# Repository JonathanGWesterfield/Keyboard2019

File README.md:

# Keyboard2019
Holds files for PCB and CAD layout for a left handed cherry mx keyboard

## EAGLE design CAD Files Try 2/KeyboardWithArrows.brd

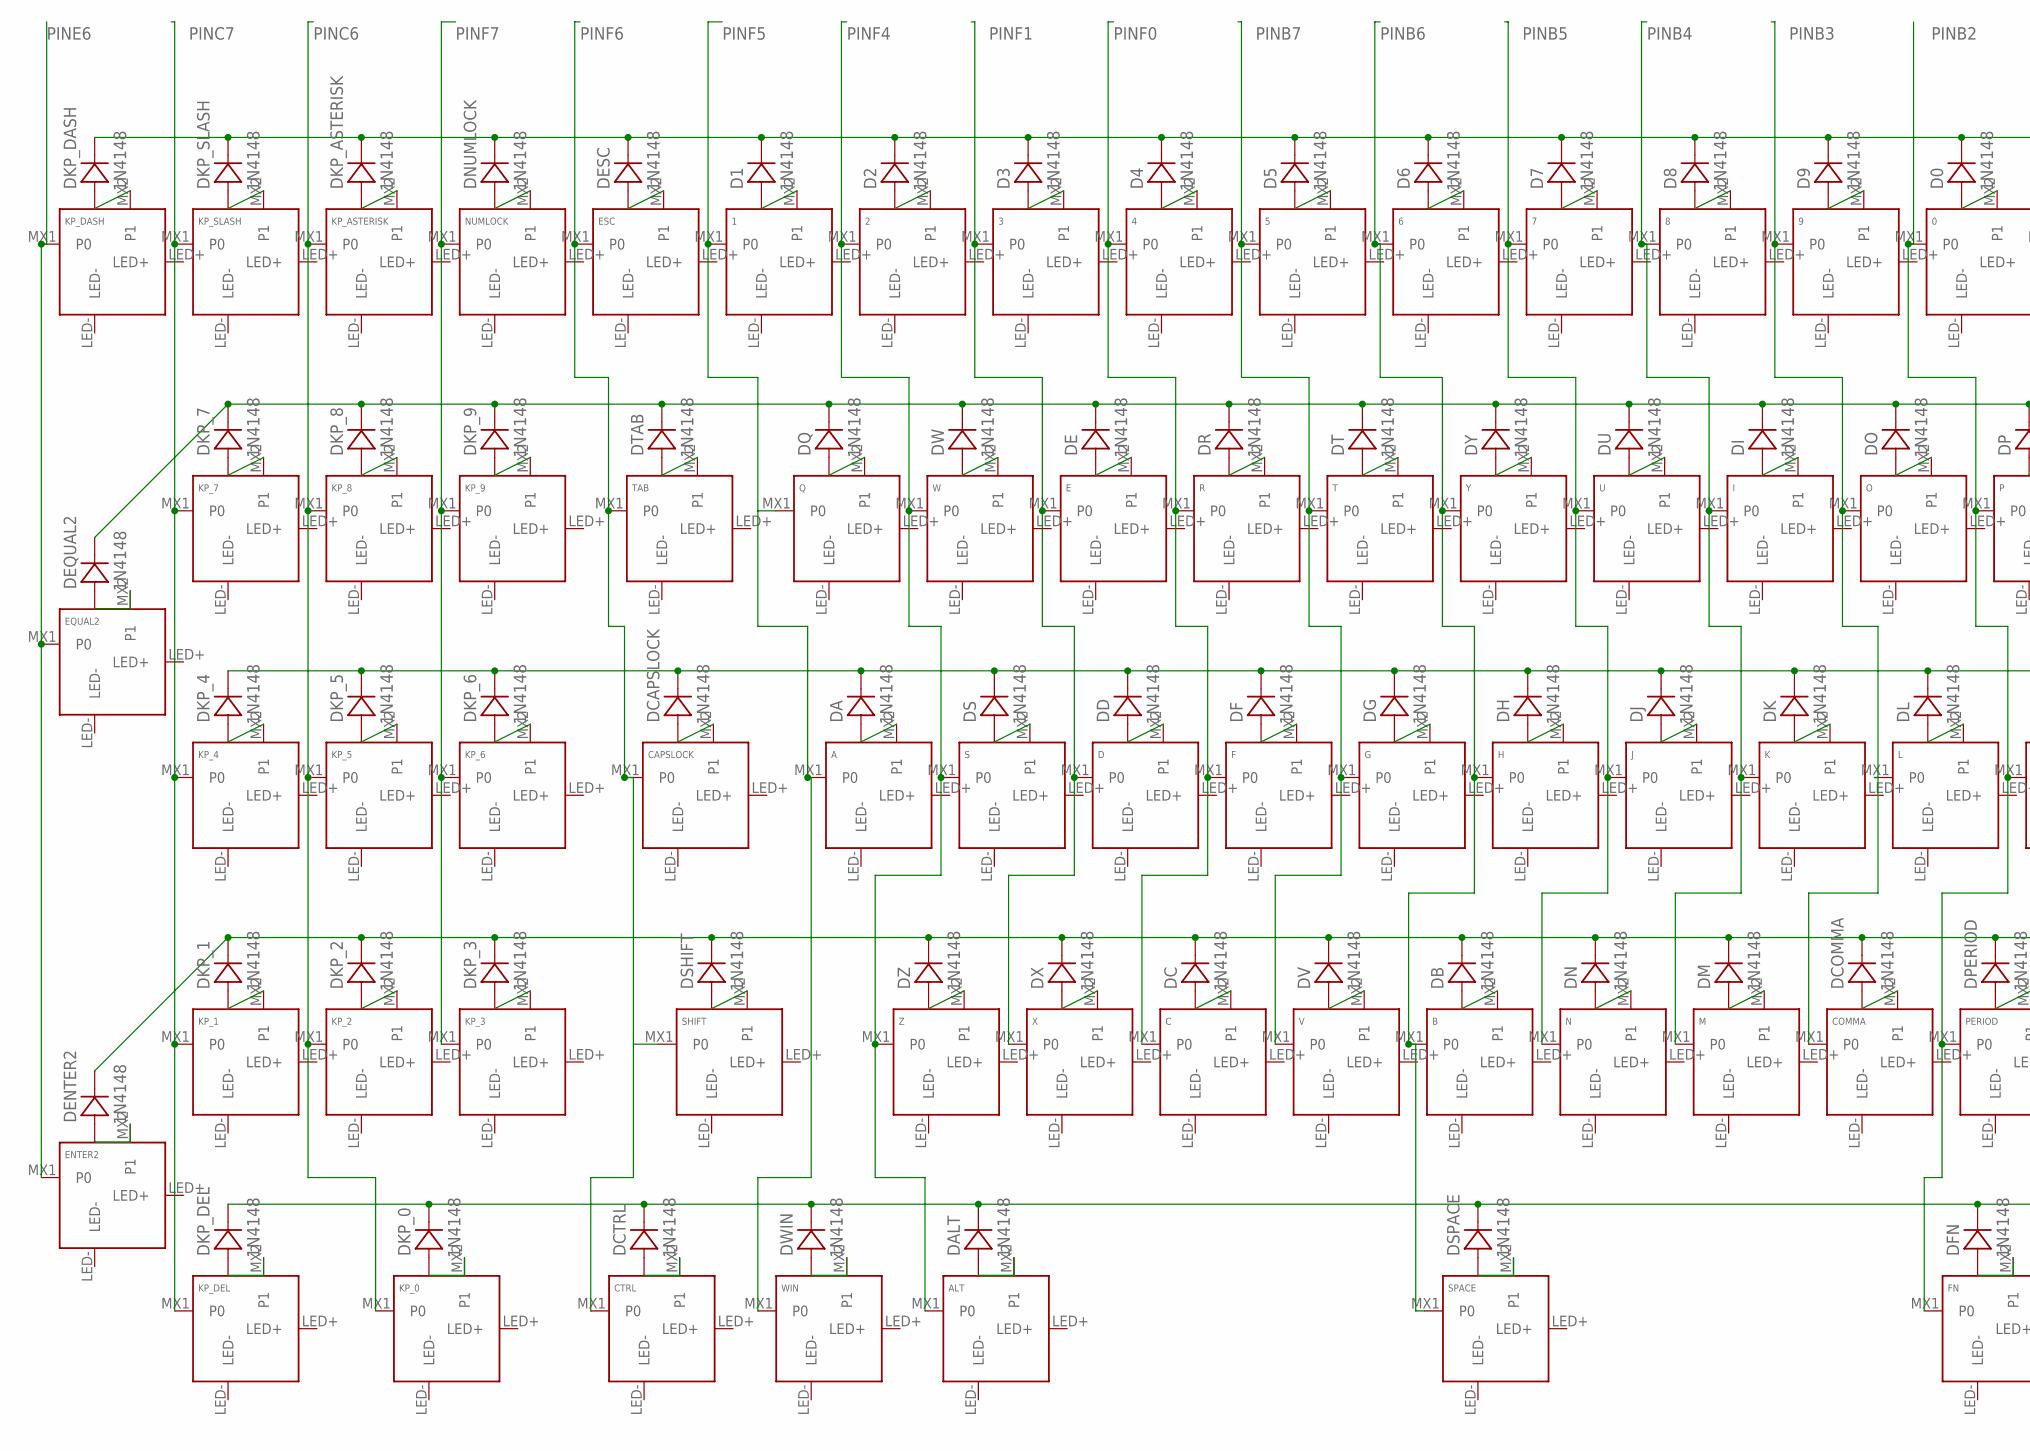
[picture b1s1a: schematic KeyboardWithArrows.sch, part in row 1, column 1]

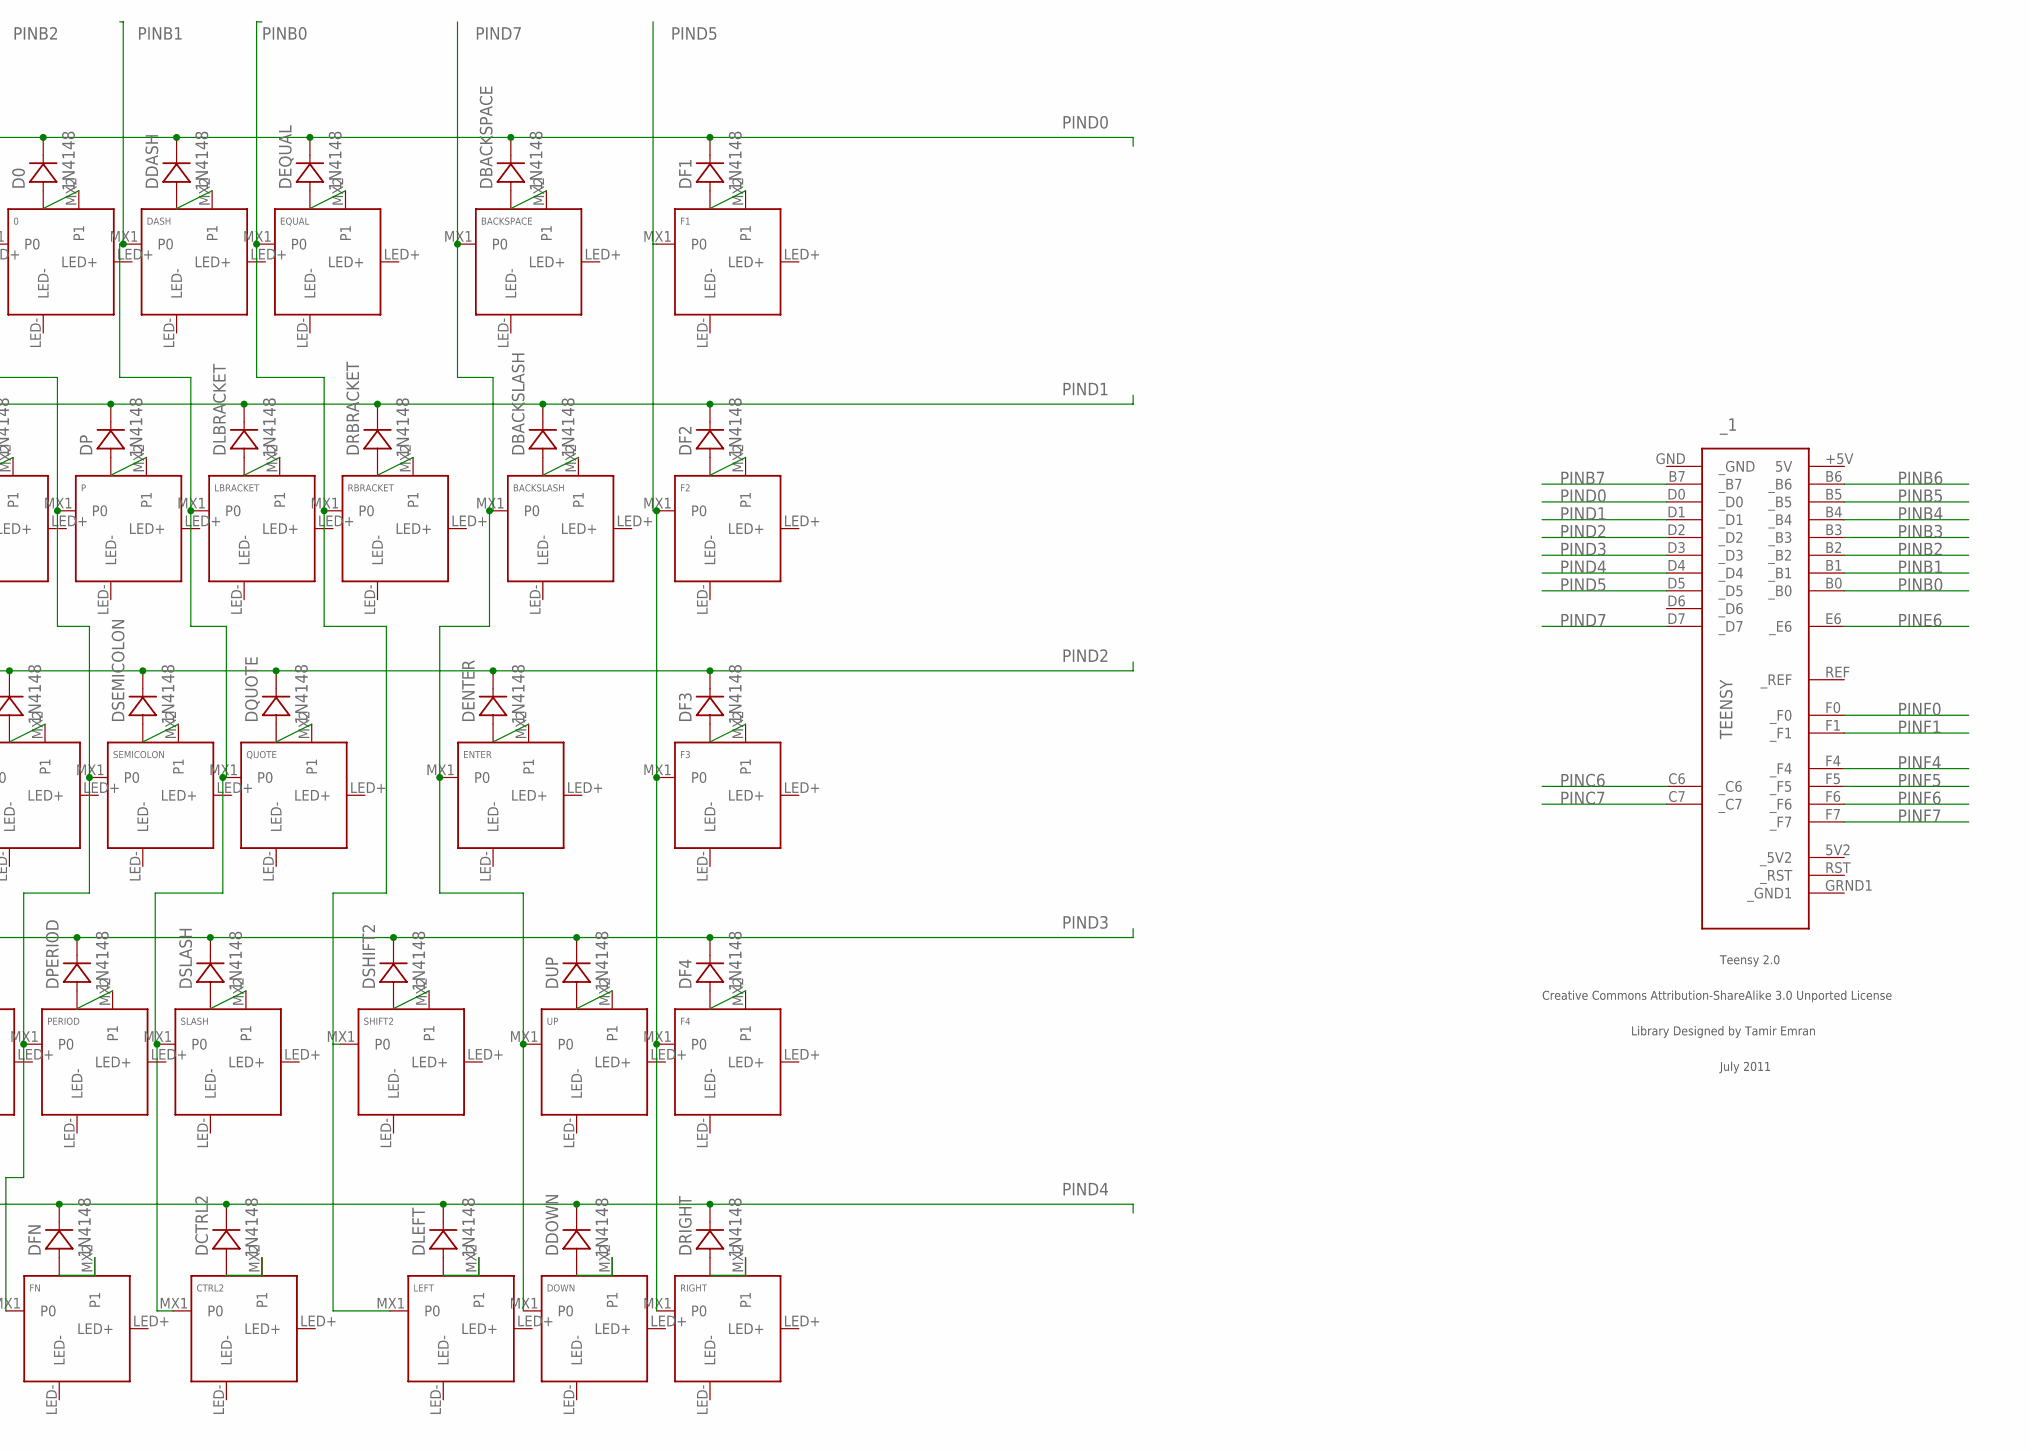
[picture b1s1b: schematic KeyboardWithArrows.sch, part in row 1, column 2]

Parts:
0, 1, 2, 3, 4, 5, 6, 7, 8, 9: KEYSWITCH-LED-MX-1U-LED; MX-1U-LED
A: KEYSWITCH-LED-MX-1U-LED; MX-1U-LED
ALT: KEYSWITCH-LED-MX-1U-LED; MX-1U-LED
B: KEYSWITCH-LED-MX-1U-LED; MX-1U-LED
BACKSLASH: KEYSWITCH-LED-MX-1U-LED; MX-1U-LED
BACKSPACE: KEYSWITCH-LED-MX-2U-LED; MX-2U-LED
C: KEYSWITCH-LED-MX-1U-LED; MX-1U-LED
CAPSLOCK: KEYSWITCH-LED-MX-1U-LED; MX-1U-LED
COMMA: KEYSWITCH-LED-MX-1U-LED; MX-1U-LED
CTRL, CTRL2: KEYSWITCH-LED-MX-1U-LED; MX-1U-LED
D: KEYSWITCH-LED-MX-1U-LED; MX-1U-LED
D0, D1, D2, D3, D4, D5, D6, D7, D8, D9: 1N4148; DO-35
DA: 1N4148; DO-35
DALT: 1N4148; DO-35
DASH: KEYSWITCH-LED-MX-1U-LED; MX-1U-LED
DB: 1N4148; DO-35
DBACKSLASH: 1N4148; DO-35
DBACKSPACE: 1N4148; DO-35
DC: 1N4148; DO-35
DCAPSLOCK: 1N4148; DO-35
DCOMMA: 1N4148; DO-35
DCTRL, DCTRL2: 1N4148; DO-35
DD: 1N4148; DO-35
DDASH: 1N4148; DO-35
DDOWN: 1N4148; DO-35
DE: 1N4148; DO-35
DENTER, DENTER2: 1N4148; DO-35
DEQUAL, DEQUAL2: 1N4148; DO-35
DESC: 1N4148; DO-35
DF, DF1, DF2, DF3, DF4: 1N4148; DO-35
DFN: 1N4148; DO-35
DG: 1N4148; DO-35
DH: 1N4148; DO-35
DI: 1N4148; DO-35
DJ: 1N4148; DO-35
DK: 1N4148; DO-35
DKP_0, DKP_1, DKP_2, DKP_3, DKP_4, DKP_5, DKP_6, DKP_7, DKP_8, DKP_9: 1N4148; DO-35
DKP_ASTERISK: 1N4148; DO-35
DKP_DASH: 1N4148; DO-35
DKP_DEL: 1N4148; DO-35
DKP_SLASH: 1N4148; DO-35
DL: 1N4148; DO-35
DLBRACKET: 1N4148; DO-35
DLEFT: 1N4148; DO-35
DM: 1N4148; DO-35
DN: 1N4148; DO-35
DNUMLOCK: 1N4148; DO-35
DO: 1N4148; DO-35
DOWN: KEYSWITCH-LED-MX-1U-LED; MX-1U-LED
DP: 1N4148; DO-35
DPERIOD: 1N4148; DO-35
DQ: 1N4148; DO-35
DQUOTE: 1N4148; DO-35
DR: 1N4148; DO-35
DRBRACKET: 1N4148; DO-35
DRIGHT: 1N4148; DO-35
DS: 1N4148; DO-35
DSEMICOLON: 1N4148; DO-35
DSHIFT, DSHIFT2: 1N4148; DO-35
DSLASH: 1N4148; DO-35
DSPACE: 1N4148; DO-35
DT: 1N4148; DO-35
DTAB: 1N4148; DO-35
DU: 1N4148; DO-35
DUP: 1N4148; DO-35
DV: 1N4148; DO-35
DW: 1N4148; DO-35
DWIN: 1N4148; DO-35
DX: 1N4148; DO-35
DY: 1N4148; DO-35
DZ: 1N4148; DO-35
E: KEYSWITCH-LED-MX-1U-LED; MX-1U-LED
ENTER: KEYSWITCH-LED-MX-2U-LED; MX-2U-LED
ENTER2: KEYSWITCH-LED-MX-1U-LED; MX-1U-LED
EQUAL, EQUAL2: KEYSWITCH-LED-MX-1U-LED; MX-1U-LED
ESC: KEYSWITCH-LED-MX-1U-LED; MX-1U-LED
F, F1, F2, F3, F4: KEYSWITCH-LED-MX-1U-LED; MX-1U-LED
FN: KEYSWITCH-LED-MX-1U-LED; MX-1U-LED
G: KEYSWITCH-LED-MX-1U-LED; MX-1U-LED
H: KEYSWITCH-LED-MX-1U-LED; MX-1U-LED
I: KEYSWITCH-LED-MX-1U-LED; MX-1U-LED
J: KEYSWITCH-LED-MX-1U-LED; MX-1U-LED
K: KEYSWITCH-LED-MX-1U-LED; MX-1U-LED
KP_0: KEYSWITCH-LED-MX-2U-LED; MX-2U-LED
KP_1, KP_2, KP_3, KP_4, KP_5, KP_6, KP_7, KP_8, KP_9: KEYSWITCH-LED-MX-1U-LED; MX-1U-LED
KP_ASTERISK: KEYSWITCH-LED-MX-1U-LED; MX-1U-LED
KP_DASH: KEYSWITCH-LED-MX-1U-LED; MX-1U-LED
KP_DEL: KEYSWITCH-LED-MX-1U-LED; MX-1U-LED
KP_SLASH: KEYSWITCH-LED-MX-1U-LED; MX-1U-LED
L: KEYSWITCH-LED-MX-1U-LED; MX-1U-LED
LBRACKET: KEYSWITCH-LED-MX-1U-LED; MX-1U-LED
LEFT: KEYSWITCH-LED-MX-1U-LED; MX-1U-LED
M: KEYSWITCH-LED-MX-1U-LED; MX-1U-LED
N: KEYSWITCH-LED-MX-1U-LED; MX-1U-LED
NUMLOCK: KEYSWITCH-LED-MX-1U-LED; MX-1U-LED
O: KEYSWITCH-LED-MX-1U-LED; MX-1U-LED
P: KEYSWITCH-LED-MX-1U-LED; MX-1U-LED
PERIOD: KEYSWITCH-LED-MX-1U-LED; MX-1U-LED
Q: KEYSWITCH-LED-MX-1U-LED; MX-1U-LED
QUOTE: KEYSWITCH-LED-MX-1U-LED; MX-1U-LED
R: KEYSWITCH-LED-MX-1U-LED; MX-1U-LED
RBRACKET: KEYSWITCH-LED-MX-1U-LED; MX-1U-LED
RIGHT: KEYSWITCH-LED-MX-1U-LED; MX-1U-LED
S: KEYSWITCH-LED-MX-1U-LED; MX-1U-LED
SEMICOLON: KEYSWITCH-LED-MX-1U-LED; MX-1U-LED
SHIFT: KEYSWITCH-LED-MX-2U-LED; MX-2U-LED
SHIFT2: KEYSWITCH-LED-MX-1U-LED; MX-1U-LED
SLASH: KEYSWITCH-LED-MX-1U-LED; MX-1U-LED
SPACE: KEYSWITCH-LED-MX-6.25U-LED; MX-6.25U-LED
T: KEYSWITCH-LED-MX-1U-LED; MX-1U-LED
TAB: KEYSWITCH-LED-MX-1U-LED; MX-1U-LED
U: KEYSWITCH-LED-MX-1U-LED; MX-1U-LED
UP: KEYSWITCH-LED-MX-1U-LED; MX-1U-LED
V: KEYSWITCH-LED-MX-1U-LED; MX-1U-LED
W: KEYSWITCH-LED-MX-1U-LED; MX-1U-LED
WIN: KEYSWITCH-LED-MX-1U-LED; MX-1U-LED
X: KEYSWITCH-LED-MX-1U-LED; MX-1U-LED
Y: KEYSWITCH-LED-MX-1U-LED; MX-1U-LED
Z: KEYSWITCH-LED-MX-1U-LED; MX-1U-LED
_1: TEENSY

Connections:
unnamed: DKP_DASH.A, KP_DASH.MX2 (P1)
unnamed: DKP_SLASH.A, KP_SLASH.MX2 (P1)
unnamed: DKP_ASTERISK.A, KP_ASTERISK.MX2 (P1)
unnamed: DNUMLOCK.A, NUMLOCK.MX2 (P1)
unnamed: 1.MX2 (P1), D1.A
unnamed: DESC.A, ESC.MX2 (P1)
unnamed: 2.MX2 (P1), D2.A
unnamed: 3.MX2 (P1), D3.A
unnamed: 4.MX2 (P1), D4.A
unnamed: 5.MX2 (P1), D5.A
unnamed: 6.MX2 (P1), D6.A
unnamed: 7.MX2 (P1), D7.A
unnamed: 8.MX2 (P1), D8.A
unnamed: 9.MX2 (P1), D9.A
unnamed: 0.MX2 (P1), D0.A
unnamed: DASH.MX2 (P1), DDASH.A
unnamed: DEQUAL.A, EQUAL.MX2 (P1)
unnamed: BACKSPACE.MX2 (P1), DBACKSPACE.A
unnamed: DF1.A, F1.MX2 (P1)
unnamed: DF2.A, F2.MX2 (P1)
unnamed: BACKSLASH.MX2 (P1), DBACKSLASH.A
unnamed: DRBRACKET.A, RBRACKET.MX2 (P1)
unnamed: DLBRACKET.A, LBRACKET.MX2 (P1)
unnamed: DP.A, P.MX2 (P1)
unnamed: DO.A, O.MX2 (P1)
unnamed: DI.A, I.MX2 (P1)
unnamed: DU.A, U.MX2 (P1)
unnamed: DY.A, Y.MX2 (P1)
unnamed: DT.A, T.MX2 (P1)
unnamed: DR.A, R.MX2 (P1)
unnamed: DE.A, E.MX2 (P1)
unnamed: DW.A, W.MX2 (P1)
unnamed: DQ.A, Q.MX2 (P1)
unnamed: DTAB.A, TAB.MX2 (P1)
unnamed: DKP_9.A, KP_9.MX2 (P1)
unnamed: DKP_8.A, KP_8.MX2 (P1)
unnamed: DKP_7.A, KP_7.MX2 (P1)
unnamed: DKP_4.A, KP_4.MX2 (P1)
unnamed: DKP_5.A, KP_5.MX2 (P1)
unnamed: DKP_6.A, KP_6.MX2 (P1)
unnamed: CAPSLOCK.MX2 (P1), DCAPSLOCK.A
unnamed: A.MX2 (P1), DA.A
unnamed: DS.A, S.MX2 (P1)
unnamed: D.MX2 (P1), DD.A
unnamed: DF.A, F.MX2 (P1)
unnamed: DG.A, G.MX2 (P1)
unnamed: DH.A, H.MX2 (P1)
unnamed: DJ.A, J.MX2 (P1)
unnamed: DK.A, K.MX2 (P1)
unnamed: DL.A, L.MX2 (P1)
unnamed: DSEMICOLON.A, SEMICOLON.MX2 (P1)
unnamed: DQUOTE.A, QUOTE.MX2 (P1)
unnamed: DENTER.A, ENTER.MX2 (P1)
unnamed: DF3.A, F3.MX2 (P1)
unnamed: DF4.A, F4.MX2 (P1)
unnamed: DUP.A, UP.MX2 (P1)
unnamed: DSHIFT2.A, SHIFT2.MX2 (P1)
unnamed: DSLASH.A, SLASH.MX2 (P1)
unnamed: DPERIOD.A, PERIOD.MX2 (P1)
unnamed: COMMA.MX2 (P1), DCOMMA.A
unnamed: DM.A, M.MX2 (P1)
unnamed: DN.A, N.MX2 (P1)
unnamed: B.MX2 (P1), DB.A
unnamed: DV.A, V.MX2 (P1)
unnamed: C.MX2 (P1), DC.A
unnamed: DX.A, X.MX2 (P1)
unnamed: DZ.A, Z.MX2 (P1)
unnamed: DSHIFT.A, SHIFT.MX2 (P1)
unnamed: DKP_3.A, KP_3.MX2 (P1)
unnamed: DKP_2.A, KP_2.MX2 (P1)
unnamed: DKP_1.A, KP_1.MX2 (P1)
unnamed: DENTER2.A, ENTER2.MX2 (P1)
unnamed: DKP_DEL.A, KP_DEL.MX2 (P1)
unnamed: DKP_0.A, KP_0.MX2 (P1)
unnamed: CTRL.MX2 (P1), DCTRL.A
unnamed: DWIN.A, WIN.MX2 (P1)
unnamed: ALT.MX2 (P1), DALT.A
unnamed: DSPACE.A, SPACE.MX2 (P1)
unnamed: DFN.A, FN.MX2 (P1)
unnamed: CTRL2.MX2 (P1), DCTRL2.A
unnamed: DLEFT.A, LEFT.MX2 (P1)
unnamed: DDOWN.A, DOWN.MX2 (P1)
unnamed: DRIGHT.A, RIGHT.MX2 (P1)
unnamed: DEQUAL2.A, EQUAL2.MX2 (P1)
PINB0: EQUAL.MX1 (P0), LEFT.MX1 (P0), RBRACKET.MX1 (P0), SHIFT2.MX1 (P0), _1.B0 (_B0)
PINB1: CTRL2.MX1 (P0), DASH.MX1 (P0), LBRACKET.MX1 (P0), QUOTE.MX1 (P0), SLASH.MX1 (P0), _1.B1 (_B1)
PINB2: 0.MX1 (P0), FN.MX1 (P0), P.MX1 (P0), PERIOD.MX1 (P0), SEMICOLON.MX1 (P0), _1.B2 (_B2)
PINB3: 9.MX1 (P0), COMMA.MX1 (P0), L.MX1 (P0), O.MX1 (P0), _1.B3 (_B3)
PINB4: 8.MX1 (P0), I.MX1 (P0), K.MX1 (P0), M.MX1 (P0), _1.B4 (_B4)
PINB5: 7.MX1 (P0), J.MX1 (P0), N.MX1 (P0), U.MX1 (P0), _1.B5 (_B5)
PINB6: 6.MX1 (P0), B.MX1 (P0), H.MX1 (P0), SPACE.MX1 (P0), Y.MX1 (P0), _1.B6 (_B6)
PINB7: 5.MX1 (P0), G.MX1 (P0), T.MX1 (P0), V.MX1 (P0), _1.B7 (_B7)
PINC6: KP_0.MX1 (P0), KP_2.MX1 (P0), KP_5.MX1 (P0), KP_8.MX1 (P0), KP_ASTERISK.MX1 (P0), _1.C6 (_C6)
PINC7: KP_1.MX1 (P0), KP_4.MX1 (P0), KP_7.MX1 (P0), KP_DEL.MX1 (P0), KP_SLASH.MX1 (P0), _1.C7 (_C7)
PIND0: D0.C, D1.C, D2.C, D3.C, D4.C, D5.C, D6.C, D7.C, D8.C, D9.C, DBACKSPACE.C, DDASH.C, DEQUAL.C, DESC.C, DF1.C, DKP_ASTERISK.C, DKP_DASH.C, DKP_SLASH.C, DNUMLOCK.C, _1.D0 (_D0)
PIND1: DBACKSLASH.C, DE.C, DEQUAL2.C, DF2.C, DI.C, DKP_7.C, DKP_8.C, DKP_9.C, DLBRACKET.C, DO.C, DP.C, DQ.C, DR.C, DRBRACKET.C, DT.C, DTAB.C, DU.C, DW.C, DY.C, _1.D1 (_D1)
PIND2: DA.C, DCAPSLOCK.C, DD.C, DENTER.C, DF.C, DF3.C, DG.C, DH.C, DJ.C, DK.C, DKP_4.C, DKP_5.C, DKP_6.C, DL.C, DQUOTE.C, DS.C, DSEMICOLON.C, _1.D2 (_D2)
PIND3: DB.C, DC.C, DCOMMA.C, DENTER2.C, DF4.C, DKP_1.C, DKP_2.C, DKP_3.C, DM.C, DN.C, DPERIOD.C, DSHIFT.C, DSHIFT2.C, DSLASH.C, DUP.C, DV.C, DX.C, DZ.C, _1.D3 (_D3)
PIND4: DALT.C, DCTRL.C, DCTRL2.C, DDOWN.C, DFN.C, DKP_0.C, DKP_DEL.C, DLEFT.C, DRIGHT.C, DSPACE.C, DWIN.C, _1.D4 (_D4)
PIND5: F1.MX1 (P0), F2.MX1 (P0), F3.MX1 (P0), F4.MX1 (P0), RIGHT.MX1 (P0), _1.D5 (_D5)
PIND7: BACKSLASH.MX1 (P0), BACKSPACE.MX1 (P0), DOWN.MX1 (P0), ENTER.MX1 (P0), UP.MX1 (P0), _1.D7 (_D7)
PINE6: ENTER2.MX1 (P0), EQUAL2.MX1 (P0), KP_DASH.MX1 (P0), _1.E6 (_E6)
PINF0: 4.MX1 (P0), C.MX1 (P0), F.MX1 (P0), R.MX1 (P0), _1.F0 (_F0)
PINF1: 3.MX1 (P0), D.MX1 (P0), E.MX1 (P0), X.MX1 (P0), _1.F1 (_F1)
PINF4: 2.MX1 (P0), ALT.MX1 (P0), S.MX1 (P0), W.MX1 (P0), Z.MX1 (P0), _1.F4 (_F4)
PINF5: 1.MX1 (P0), A.MX1 (P0), Q.MX1 (P0), WIN.MX1 (P0), _1.F5 (_F5)
PINF6: CAPSLOCK.MX1 (P0), CTRL.MX1 (P0), ESC.MX1 (P0), SHIFT.MX1 (P0), TAB.MX1 (P0), _1.F6 (_F6)
PINF7: KP_3.MX1 (P0), KP_6.MX1 (P0), KP_9.MX1 (P0), NUMLOCK.MX1 (P0), _1.F7 (_F7)

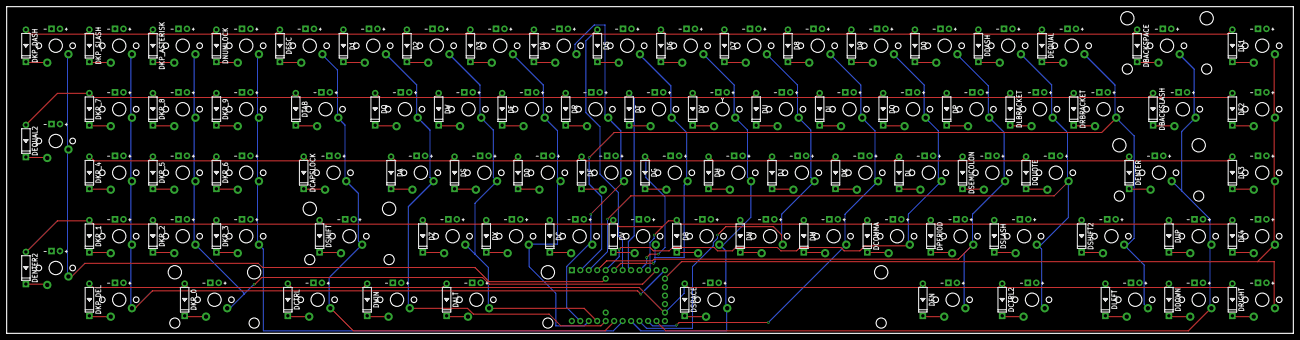
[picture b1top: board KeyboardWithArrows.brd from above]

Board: 2 copper layers, 386.0 x 98.0 mm, 169 parts (1 on the bottom side), 108 nets.

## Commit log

2018-12-16 Gitignore for macos, linux, kicad, eagle, windows, microsoftoffice
2018-12-16 Added Teensy Pinout, Teensy Eagle Files, Plate CAD layouts and started pcb schematic
2019-02-10 Update layout
2019-02-10 Changed CAD files
2019-02-14 Added more to keyboard schematic
2019-02-16 Found a tool to autogenerate the board layout and added those files
2019-02-19 Added and connected nets
2019-03-19 Changed Plate files after modifying keyboard layout
2019-03-19 Fixed an issue where 2 columns were connected together
2019-04-04 Started new design
2019-04-05 Added wires to schematics. Need to wire to teensy pins
2019-04-10 Added traces to board schematic
2019-04-11 Fixed part of board where a key was missing a connection
2019-12-28 Added the gerber files for the pcb and added the CAD plate files (Used fedc to machine the parts and they are weird).
2019-12-28 Added the microcontroller files for my latest layout
2019-12-28 CAD Files Try 2/112c735c7e5c95c869da9888d3746e6e.schematic.scr
2019-12-28 Added the PCB layout files and the schematic script that lays out the schematic based off of the layout from the website
2019-12-28 Started the blog for the keyboard
2019-12-28 Changed the name of the blog site because github wouldn't recognize it unless it is named 'docs/'
2019-12-28 Tried updating the theme gemfile so it will build on gh-pages
2019-12-29 Second try to see if updating the Gemfile works for gh-pages
2019-12-30 Uploaded a (hopefully) working jekyll site using the swiss theme. Also created the first post on why I built a keyboard in the first place.
2019-12-30 Updated the website and created another separate post for the first keyboard attempt.
2019-12-30 Updated the base url in the _config.yml file to hopefully resolve the autogenerated posts showing up on the site.
2019-12-31 Attempting to fix the base url for posts to route correclty again.
2019-12-31 Added some more stuff from the original repository so this should hopefully fix the post link issues.
2020-02-26 Bump nokogiri from 1.10.7 to 1.10.8 in /docs
    Bumps [nokogiri](https://github.com/sparklemotion/nokogiri) from 1.10.7 to 1.10.8.
    - [Release notes](https://github.com/sparklemotion/nokogiri/releases)
    - [Changelog](https://github.com/sparklemotion/nokogiri/blob/master/CHANGELOG.md)
    - [Commits](https://github.com/sparklemotion/nokogiri/compare/v1.10.7...v1.10.8)
2020-04-21 Fixed typo that caused spamming of '+', '-', and 'enter' whenwaking computer from sleep. Also fixed typo in Keymap_poker.c that prevented '0' key on numpad from working.
2020-05-26 Bump activesupport from 6.0.2.1 to 6.0.3.1 in /docs
    Bumps [activesupport](https://github.com/rails/rails) from 6.0.2.1 to 6.0.3.1.
    - [Release notes](https://github.com/rails/rails/releases)
    - [Changelog](https://github.com/rails/rails/blob/v6.0.3.1/activesupport/CHANGELOG.md)
    - [Commits](https://github.com/rails/rails/compare/v6.0.2.1...v6.0.3.1)
2021-05-20 Bump nokogiri from 1.10.7 to 1.11.5 in /docs
    Bumps [nokogiri](https://github.com/sparklemotion/nokogiri) from 1.10.7 to 1.11.5.
    - [Release notes](https://github.com/sparklemotion/nokogiri/releases)
    - [Changelog](https://github.com/sparklemotion/nokogiri/blob/main/CHANGELOG.md)
    - [Commits](https://github.com/sparklemotion/nokogiri/compare/v1.10.7...v1.11.5)
2021-07-13 Bump addressable from 2.7.0 to 2.8.0 in /gh-pages
    Bumps [addressable](https://github.com/sporkmonger/addressable) from 2.7.0 to 2.8.0.
    - [Release notes](https://github.com/sporkmonger/addressable/releases)
    - [Changelog](https://github.com/sporkmonger/addressable/blob/main/CHANGELOG.md)
    - [Commits](https://github.com/sporkmonger/addressable/compare/addressable-2.7.0...addressable-2.8.0)
    ---
    updated-dependencies:
2021-07-13 Bump addressable from 2.7.0 to 2.8.0 in /docs
    Bumps [addressable](https://github.com/sporkmonger/addressable) from 2.7.0 to 2.8.0.
    - [Release notes](https://github.com/sporkmonger/addressable/releases)
    - [Changelog](https://github.com/sporkmonger/addressable/blob/main/CHANGELOG.md)
    - [Commits](https://github.com/sporkmonger/addressable/compare/addressable-2.7.0...addressable-2.8.0)
    ---
    updated-dependencies:
2021-09-28 Bump nokogiri from 1.10.7 to 1.12.5 in /docs
    Bumps [nokogiri](https://github.com/sparklemotion/nokogiri) from 1.10.7 to 1.12.5.
    - [Release notes](https://github.com/sparklemotion/nokogiri/releases)
    - [Changelog](https://github.com/sparklemotion/nokogiri/blob/main/CHANGELOG.md)
    - [Commits](https://github.com/sparklemotion/nokogiri/compare/v1.10.7...v1.12.5)
    ---
    updated-dependencies:
2022-02-26 Bump nokogiri from 1.10.7 to 1.13.3 in /docs
    Bumps [nokogiri](https://github.com/sparklemotion/nokogiri) from 1.10.7 to 1.13.3.
    - [Release notes](https://github.com/sparklemotion/nokogiri/releases)
    - [Changelog](https://github.com/sparklemotion/nokogiri/blob/main/CHANGELOG.md)
    - [Commits](https://github.com/sparklemotion/nokogiri/compare/v1.10.7...v1.13.3)
    ---
    updated-dependencies:
2022-04-12 Bump nokogiri from 1.10.7 to 1.13.4 in /docs
    Bumps [nokogiri](https://github.com/sparklemotion/nokogiri) from 1.10.7 to 1.13.4.
    - [Release notes](https://github.com/sparklemotion/nokogiri/releases)
    - [Changelog](https://github.com/sparklemotion/nokogiri/blob/v1.13.4/CHANGELOG.md)
    - [Commits](https://github.com/sparklemotion/nokogiri/compare/v1.10.7...v1.13.4)
    ---
    updated-dependencies:
2022-05-18 Bump nokogiri from 1.10.7 to 1.13.6 in /docs
    Bumps [nokogiri](https://github.com/sparklemotion/nokogiri) from 1.10.7 to 1.13.6.
    - [Release notes](https://github.com/sparklemotion/nokogiri/releases)
    - [Changelog](https://github.com/sparklemotion/nokogiri/blob/main/CHANGELOG.md)
    - [Commits](https://github.com/sparklemotion/nokogiri/compare/v1.10.7...v1.13.6)
    ---
    updated-dependencies:
2022-07-22 Bump tzinfo from 1.2.6 to 1.2.10 in /gh-pages
    Bumps [tzinfo](https://github.com/tzinfo/tzinfo) from 1.2.6 to 1.2.10.
    - [Release notes](https://github.com/tzinfo/tzinfo/releases)
    - [Changelog](https://github.com/tzinfo/tzinfo/blob/master/CHANGES.md)
    - [Commits](https://github.com/tzinfo/tzinfo/compare/v1.2.6...v1.2.10)
    ---
    updated-dependencies:
2022-07-22 Bump tzinfo from 1.2.6 to 1.2.10 in /docs
    Bumps [tzinfo](https://github.com/tzinfo/tzinfo) from 1.2.6 to 1.2.10.
    - [Release notes](https://github.com/tzinfo/tzinfo/releases)
    - [Changelog](https://github.com/tzinfo/tzinfo/blob/master/CHANGES.md)
    - [Commits](https://github.com/tzinfo/tzinfo/compare/v1.2.6...v1.2.10)
    ---
    updated-dependencies:
2022-10-06 Bump addressable from 2.7.0 to 2.8.1 in /gh-pages
    Bumps [addressable](https://github.com/sporkmonger/addressable) from 2.7.0 to 2.8.1.
    - [Release notes](https://github.com/sporkmonger/addressable/releases)
    - [Changelog](https://github.com/sporkmonger/addressable/blob/main/CHANGELOG.md)
    - [Commits](https://github.com/sporkmonger/addressable/compare/addressable-2.7.0...addressable-2.8.1)
    ---
    updated-dependencies:
2022-10-06 Bump addressable from 2.7.0 to 2.8.1 in /docs
    Bumps [addressable](https://github.com/sporkmonger/addressable) from 2.7.0 to 2.8.1.
    - [Release notes](https://github.com/sporkmonger/addressable/releases)
    - [Changelog](https://github.com/sporkmonger/addressable/blob/main/CHANGELOG.md)
    - [Commits](https://github.com/sporkmonger/addressable/compare/addressable-2.7.0...addressable-2.8.1)
    ---
    updated-dependencies:
2022-10-20 Bump nokogiri from 1.10.7 to 1.13.9 in /docs
    Bumps [nokogiri](https://github.com/sparklemotion/nokogiri) from 1.10.7 to 1.13.9.
    - [Release notes](https://github.com/sparklemotion/nokogiri/releases)
    - [Changelog](https://github.com/sparklemotion/nokogiri/blob/main/CHANGELOG.md)
    - [Commits](https://github.com/sparklemotion/nokogiri/compare/v1.10.7...v1.13.9)
    ---
    updated-dependencies:
2023-01-20 Bump activesupport from 6.0.2.1 to 6.0.6.1 in /docs
    Bumps [activesupport](https://github.com/rails/rails) from 6.0.2.1 to 6.0.6.1.
    - [Release notes](https://github.com/rails/rails/releases)
    - [Changelog](https://github.com/rails/rails/blob/v7.0.4.1/activesupport/CHANGELOG.md)
    - [Commits](https://github.com/rails/rails/compare/v6.0.2.1...v6.0.6.1)
    ---
    updated-dependencies:
2023-04-11 Bump nokogiri from 1.10.7 to 1.14.3 in /docs
    Bumps [nokogiri](https://github.com/sparklemotion/nokogiri) from 1.10.7 to 1.14.3.
    - [Release notes](https://github.com/sparklemotion/nokogiri/releases)
    - [Changelog](https://github.com/sparklemotion/nokogiri/blob/main/CHANGELOG.md)
    - [Commits](https://github.com/sparklemotion/nokogiri/compare/v1.10.7...v1.14.3)
    ---
    updated-dependencies:

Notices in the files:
parts and their libraries:
teensy: Licensed Under Creative Commons
teensy: Creative Commons Attribution-ShareAlike 3.0 Unported License
teensy: Licensed Under Creative Commons Attribution-ShareAlike 3.0 Unported (CC BY-SA 3.0)
